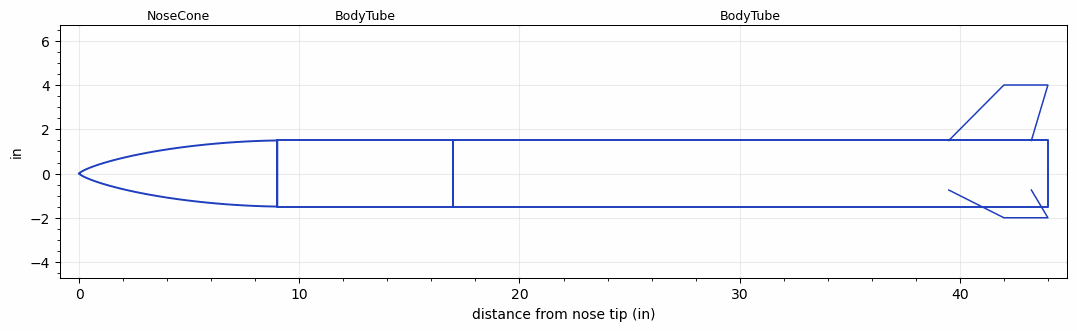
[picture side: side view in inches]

<RASAeroDocument>
 <FileVersion>2</FileVersion>
 <RocketDesign>
  <NoseCone>
   <Length>9</Length>
   <Diameter>3</Diameter>
   <Shape>LV-Haack</Shape>
   <Location>0</Location>
  </NoseCone>
  <BodyTube>
   <Length>8</Length>
   <Diameter>3</Diameter>
   <Location>9</Location>
  </BodyTube>
  <BodyTube>
   <Length>27</Length>
   <Diameter>3</Diameter>
   <RailGuideDiameter>0.438</RailGuideDiameter>
   <RailGuideHeight>0.298</RailGuideHeight>
   <Location>17</Location>
   <Fin>
    <Count>3</Count>
    <Chord>3.75</Chord>
    <Span>2.5196</Span>
    <SweepDistance>2.5</SweepDistance>
    <TipChord>2</TipChord>
    <Thickness>0.25</Thickness>
    <Location>4.5</Location>
    <AirfoilSection>Single Wedge</AirfoilSection>
   </Fin>
  </BodyTube>
  <Surface>Smooth (Zero Roughness)</Surface>
  <ModifiedBarrowman>True</ModifiedBarrowman>
  <Turbulence>True</Turbulence>
  <SustainerNozzle>1</SustainerNozzle>
  <UseBooster1>False</UseBooster1>
  <UseBooster2>False</UseBooster2>
 </RocketDesign>
 <LaunchSite>
  <Altitude>708</Altitude>
  <Pressure>0</Pressure>
  <RodAngle>6</RodAngle>
  <RodLength>2.2</RodLength>
  <Temperature>74</Temperature>
  <WindSpeed>33</WindSpeed>
 </LaunchSite>
 <Recovery>
  <Altitude1>1000</Altitude1>
  <Altitude2>1000</Altitude2>
  <DeviceType1>Parachute</DeviceType1>
  <DeviceType2>None</DeviceType2>
  <Event1>True</Event1>
  <Event2>False</Event2>
  <Size1>44.88</Size1>
  <Size2>1</Size2>
  <EventType1>Apogee</EventType1>
  <EventType2>None</EventType2>
  <CD1>1</CD1>
  <CD2>1.33</CD2>
 </Recovery>
 <SimulationList>
  <Simulation>
   <SustainerEngine>H97J  (AT)</SustainerEngine>
   <SustainerLaunchWt>3.23</SustainerLaunchWt>
   <SustainerNozzleDiameter>1.21</SustainerNozzleDiameter>
   <SustainerCG>21.97</SustainerCG>
   <SustainerIgnitionDelay>0</SustainerIgnitionDelay>
   <Booster1SeparationDelay>0</Booster1SeparationDelay>
   <Booster1IgnitionDelay>0</Booster1IgnitionDelay>
   <IncludeBooster1>False</IncludeBooster1>
   <Booster2Delay>0</Booster2Delay>
   <IncludeBooster2>False</IncludeBooster2>
   <TimetoApogee>11.73017</TimetoApogee>
   <MaxAltitude>3034.074</MaxAltitude>
   <MaxVelocity>729.4398</MaxVelocity>
   <OptimumWt>1.37275</OptimumWt>
   <OptimumMaxAlt>1.37275</OptimumMaxAlt>
  </Simulation>
  <Simulation>
   <SustainerEngine>H97J  (AT)</SustainerEngine>
   <SustainerLaunchWt>0</SustainerLaunchWt>
   <SustainerCG>0</SustainerCG>
   <SustainerIgnitionDelay>0</SustainerIgnitionDelay>
   <Booster1SeparationDelay>0</Booster1SeparationDelay>
   <Booster1IgnitionDelay>0</Booster1IgnitionDelay>
   <IncludeBooster1>False</IncludeBooster1>
   <Booster2Delay>0</Booster2Delay>
   <IncludeBooster2>False</IncludeBooster2>
  </Simulation>
 </SimulationList>
</RASAeroDocument>
